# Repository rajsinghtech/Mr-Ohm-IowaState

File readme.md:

## BetterBots Project
The BetterBots project is a robot designed to teach coding and engineering concepts. The goal of the Senior Design team at Iowa State is to develop the FPGA portion of the robot.

## Folder Structure
The project's GitHub repository contains the following folders:
```
root/
├── Board_Design_Files/
│   ├── Active-ADC/
│   ├── Passive-ADC/
│   ├── ActiveGerber.zip
│   ├── PassiveGerber.zip
│   └── bom.xlsx
├── Simulation/
│   └── LTSpice/
└── Digital_Design_Files/
    ├── Orbtrace/
    └── betterbots.tar
```

# Board_Design_Files: 
This folder contains the design files for the board. The files are divided into two subfolders, Active-ADC and Passive-ADC, which contain the active and passive components, respectively. The ActiveGerber.zip and PassiveGerber.zip files contain the Gerber files necessary for manufacturing the board. The bom.xlsx file lists all the components required for the board design.

# Simulation: 
This folder contains the LTSpice simulation files for the project.

# Digital_Design_Files: 
This folder contains the design files for the digital portion of the project. The Orbtrace folder contains the source code for the Orbtrace debugger. The betterbots.tar file contains the code for the BetterBots project.

## Project Details
The project utilizes an ECPIX-5 FPGA to take in multiple types of input devices and apply logic to output the data to another device, such as a Raspberry Pi. This includes an FPGA RISC-v core, Camera subsystem, Fast Fourier Transform, and USB stack. The team envisions executing the project according to the schematic on the right.

The BetterBots project aims to teach coding and engineering concepts through hands-on experimentation with a robot.

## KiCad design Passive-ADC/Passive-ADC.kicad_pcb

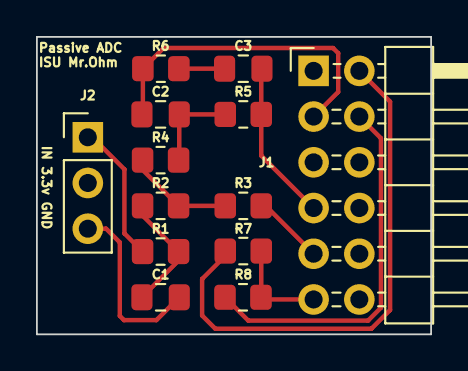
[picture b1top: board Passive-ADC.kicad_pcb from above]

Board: 4 copper layers, 21.9 x 16.5 mm, 13 parts (0 on the bottom side), 10 nets.

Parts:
C1: .1u; C_0805_2012Metric_Pad1.18x1.45mm_HandSolder
C2: 470p; C_0805_2012Metric_Pad1.18x1.45mm_HandSolder
C3: 68p; C_0805_2012Metric_Pad1.18x1.45mm_HandSolder
J1: FPGA Terminal; PinHeader_2x06_P2.54mm_Horizontal
J2: ADC Terminal; PinHeader_1x03_P2.54mm_Vertical
R1: 100; R_0805_2012Metric_Pad1.20x1.40mm_HandSolder
R2: 18k; R_0805_2012Metric_Pad1.20x1.40mm_HandSolder
R3, R4: 15k; R_0805_2012Metric_Pad1.20x1.40mm_HandSolder
R5: 8k; R_0805_2012Metric_Pad1.20x1.40mm_HandSolder
R6: 1.1k; R_0805_2012Metric_Pad1.20x1.40mm_HandSolder
R7: 6.8k; R_0805_2012Metric_Pad1.20x1.40mm_HandSolder
R8: 3.3k; R_0805_2012Metric_Pad1.20x1.40mm_HandSolder

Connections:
/3.3V: J1.1, J1.2, J2.2, R7.1
/FPGA-IN: J1.9, R3.1
/FPGA-OUT: C3.1, J1.7, R5.2
/FPGA-REF: J1.11, R7.2, R8.1
/Sensor-IN: J2.1, R1.1
GND: C1.2, C2.2, J1.3, J1.4, J2.3, R6.1, R8.2
unnamed: C1.1, R1.2, R2.1
unnamed: C2.1, R4.2, R5.1
unnamed: C3.2, R6.2
unnamed: R2.2, R3.2, R4.1

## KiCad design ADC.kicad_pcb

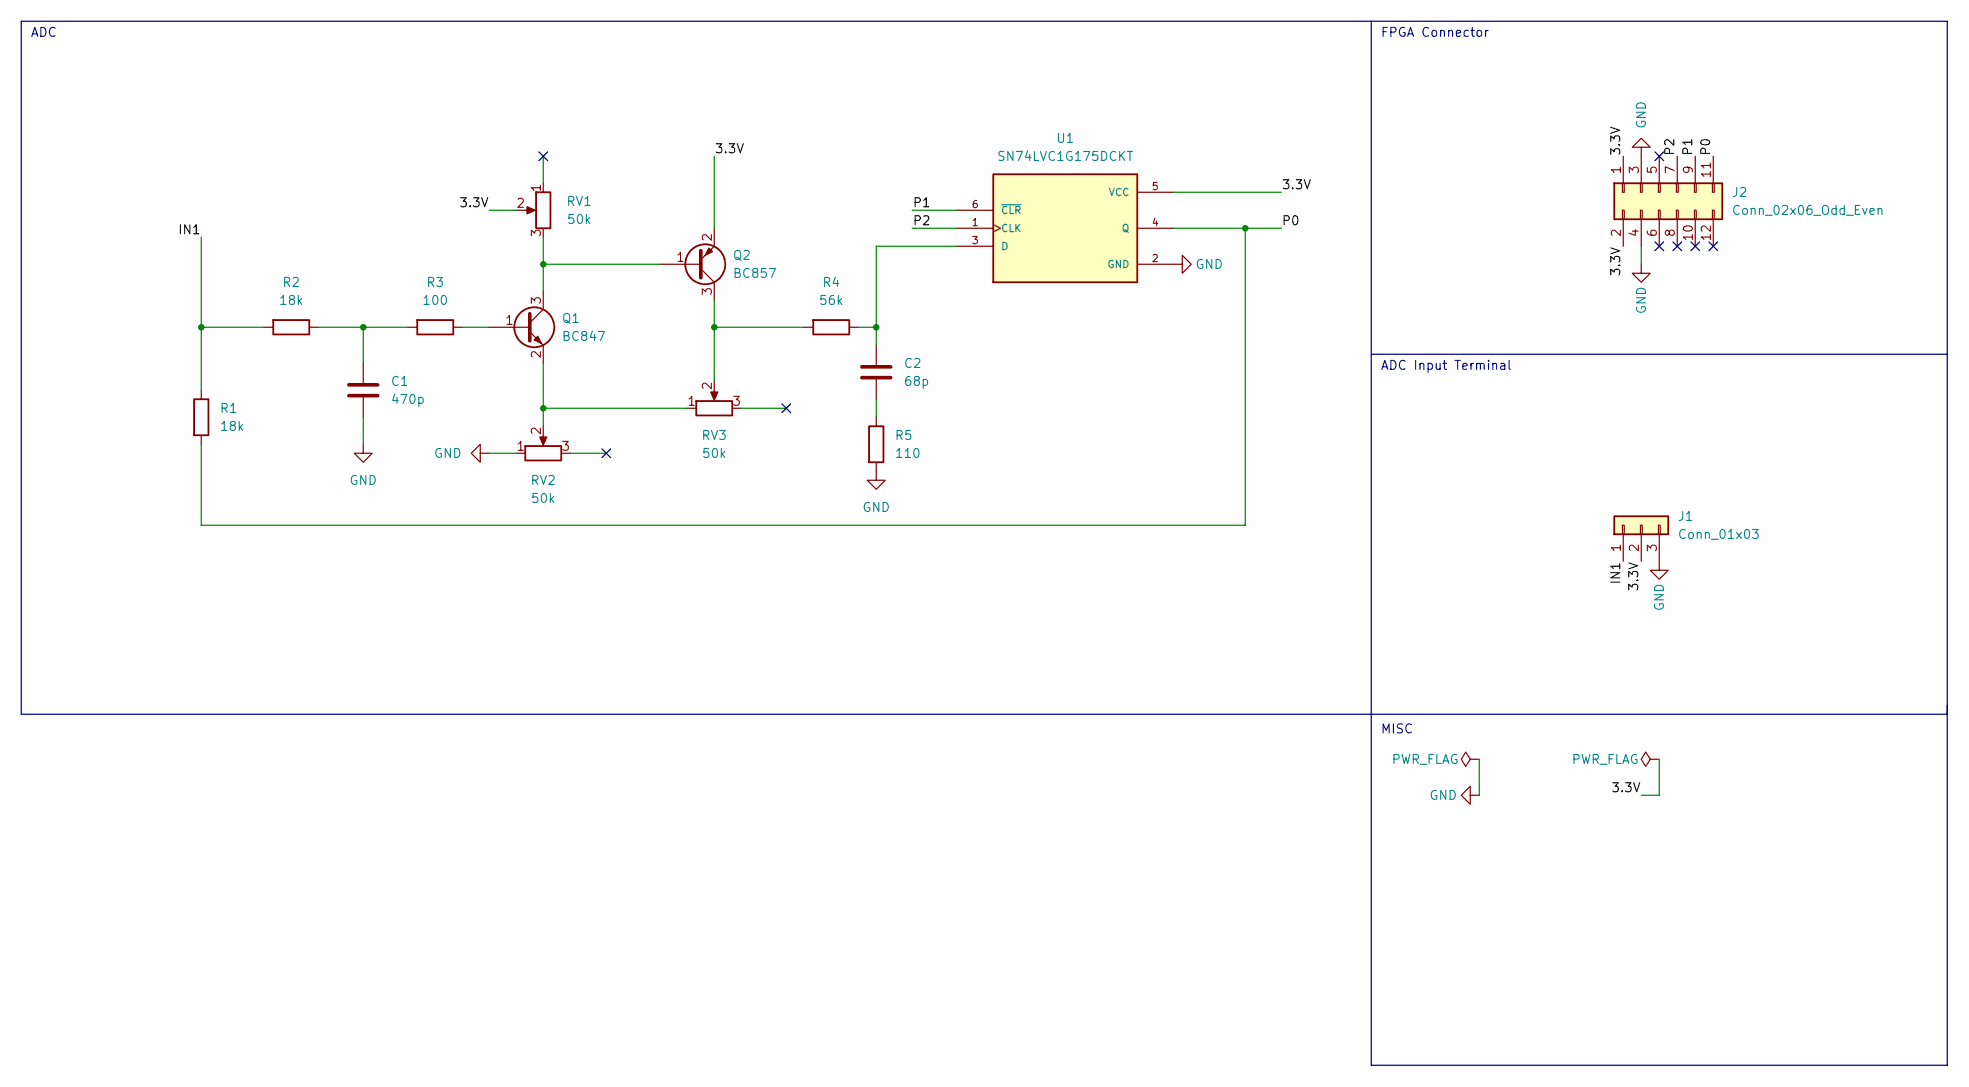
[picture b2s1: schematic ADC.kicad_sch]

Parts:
C1: 470p; R_Axial_DIN0207_L6.3mm_D2.5mm_P10.16mm_Horizontal
C2: 68p; R_Axial_DIN0207_L6.3mm_D2.5mm_P10.16mm_Horizontal
J1: Conn_01x03; PinHeader_1x03_P1.00mm_Vertical
J2: Conn_02x06_Odd_Even; PinHeader_2x06_P1.00mm_Horizontal
Q1: BC847; SOT-23
Q2: BC857; SOT-23
R1, R2: 18k; R_Axial_DIN0207_L6.3mm_D2.5mm_P10.16mm_Horizontal
R3: 100; R_Axial_DIN0207_L6.3mm_D2.5mm_P10.16mm_Horizontal
R4: 56k; R_Axial_DIN0207_L6.3mm_D2.5mm_P10.16mm_Horizontal
R5: 110; R_Axial_DIN0207_L6.3mm_D2.5mm_P10.16mm_Horizontal
RV1, RV2, RV3: 50k; Potentiometer_ACP_CA9-V10_Vertical_Hole
U1: SN74LVC1G175DCKT; SOT65P210X110-6N; PARTREV G

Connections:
/3.3V: J1.2, J2.1, J2.2, Q2.2 (E), RV1.2, U1.5 (VCC)
/IN1: J1.1, R1.1, R2.2
/P0: J2.11, R1.2, U1.4 (Q)
/P1: J2.9, U1.6 (~CLR)
/P2: J2.7, U1.1 (CLK)
GND: C1.2, J1.3, J2.3, J2.4, R5.2, RV2.1, U1.2 (GND)
unnamed: C1.1, R2.1, R3.2
unnamed: C2.1, R4.1, U1.3 (D)
unnamed: C2.2, R5.1
unnamed: Q1.1 (B), R3.1
unnamed: Q1.2 (E), RV2.2, RV3.1
unnamed: Q1.3 (C), Q2.1 (B), RV1.3
unnamed: Q2.3 (C), R4.2, RV3.2

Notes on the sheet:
MISC
ADC
ADC Input Terminal
FPGA Connector

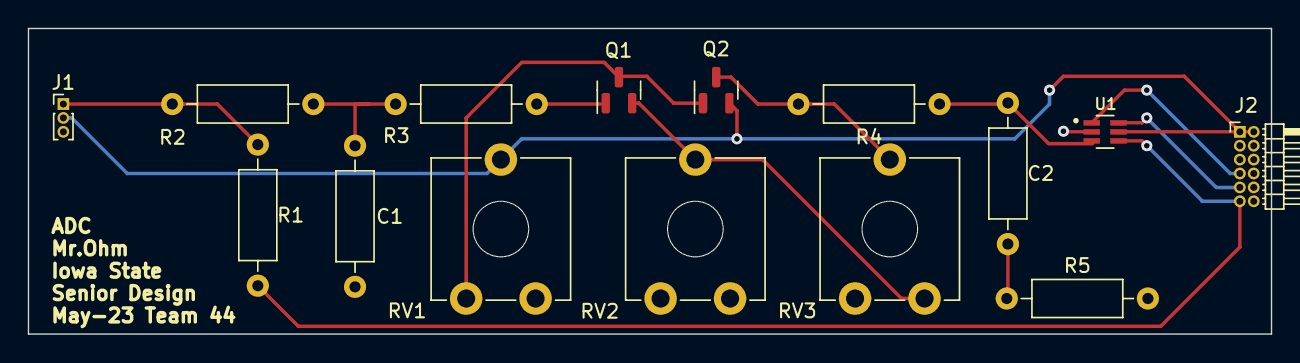
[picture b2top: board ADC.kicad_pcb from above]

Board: 2 copper layers, 89.5 x 22.0 mm, 15 parts (0 on the bottom side), 13 nets.

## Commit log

2023-02-27 Init
2023-02-28 Fixed C2 connections
2023-03-18 Hotfix
2023-03-18 Added Readme
2023-03-18 Added spacing to readme
2023-03-18 Removed all kicads
2023-03-18 Readding kicads
2023-03-18 Updated kicad
2023-03-21 Added BOM
2023-03-27 Added part numbers and switched footprints to SMD
2023-03-28 Updated part numbers
2023-03-28 Updated schematic for full SMD components with part numbers
2023-03-28 Updated footprints
2023-03-30 Updated footprints too all 0805 standard
2023-04-03 Replaced passive adc with active adc
2023-04-03 Update passive curcuit with new resistor values
2023-04-04 Close to final pcb adjusted footprints and layout design incorperating voltage divider
2023-04-05 Updated models with new schematic details
2023-04-05 Added Gerbers
2023-04-08 Finalized ADC ordering
2023-04-10 Added FPGA portion
2023-05-02 Create betterbots.tar
    Docker Image
2023-05-02 Cleanup
2025-08-06 Update actions/cache action to v4
